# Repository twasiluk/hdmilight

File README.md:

hdmilight
=========

[2016-03-23] This repo has been obsolete for a long time.

Go to http://hacks.esar.org.uk/hdmi-light-v2/ and https://github.com/esar
*************************

Papilio FPGA HDMI Ambilight project forked from http://hacks.esar.org.uk/hg/hdmilight/file/tip/

For latest version, go to http://hacks.esar.org.uk/hdmi-light/

How to use:

1) Manufacture the HDMI receiver board that can be found in the 'board' directory (CADSoft Eagle format)

2) Open the 'fpga/hdmilight.xise' project in Xilinx ISE

2a) Regenerate the IP cores: in the Hierarchy panel, expand the tree and select the conf, line_buffer and resultBuffer entries one by one and run the "Regenerate Core" process in the panel below

2b) Generate the bit file

3) Edit 'firmware/config_lights.h' to set light definitions

4) Edit 'Makefile' in the top level directory and set the DATA2MEM path for the Xilinx data2mem tooli location on your system

5) Run 'make' in the top level directory, which will build 'tools/makemem', then the firmware image, then merge the firware image into the fpga bitfile. The final result should be hdmilight.bit in the top level directory

6) Upload hdmilight.bit to a Papilio One 250K FPGA board

7) Install the HDMI receiver board on to the Papilio board

8) Connect LED strips to output pins

9) Open a serial terminal to the Papilio

10) Give the command to initialise I2C: I I
   
11) Give the command to configure the light definitions and the ADV611 chip: I C

12) Connect HDMI source to receiver board

13) It should now be working

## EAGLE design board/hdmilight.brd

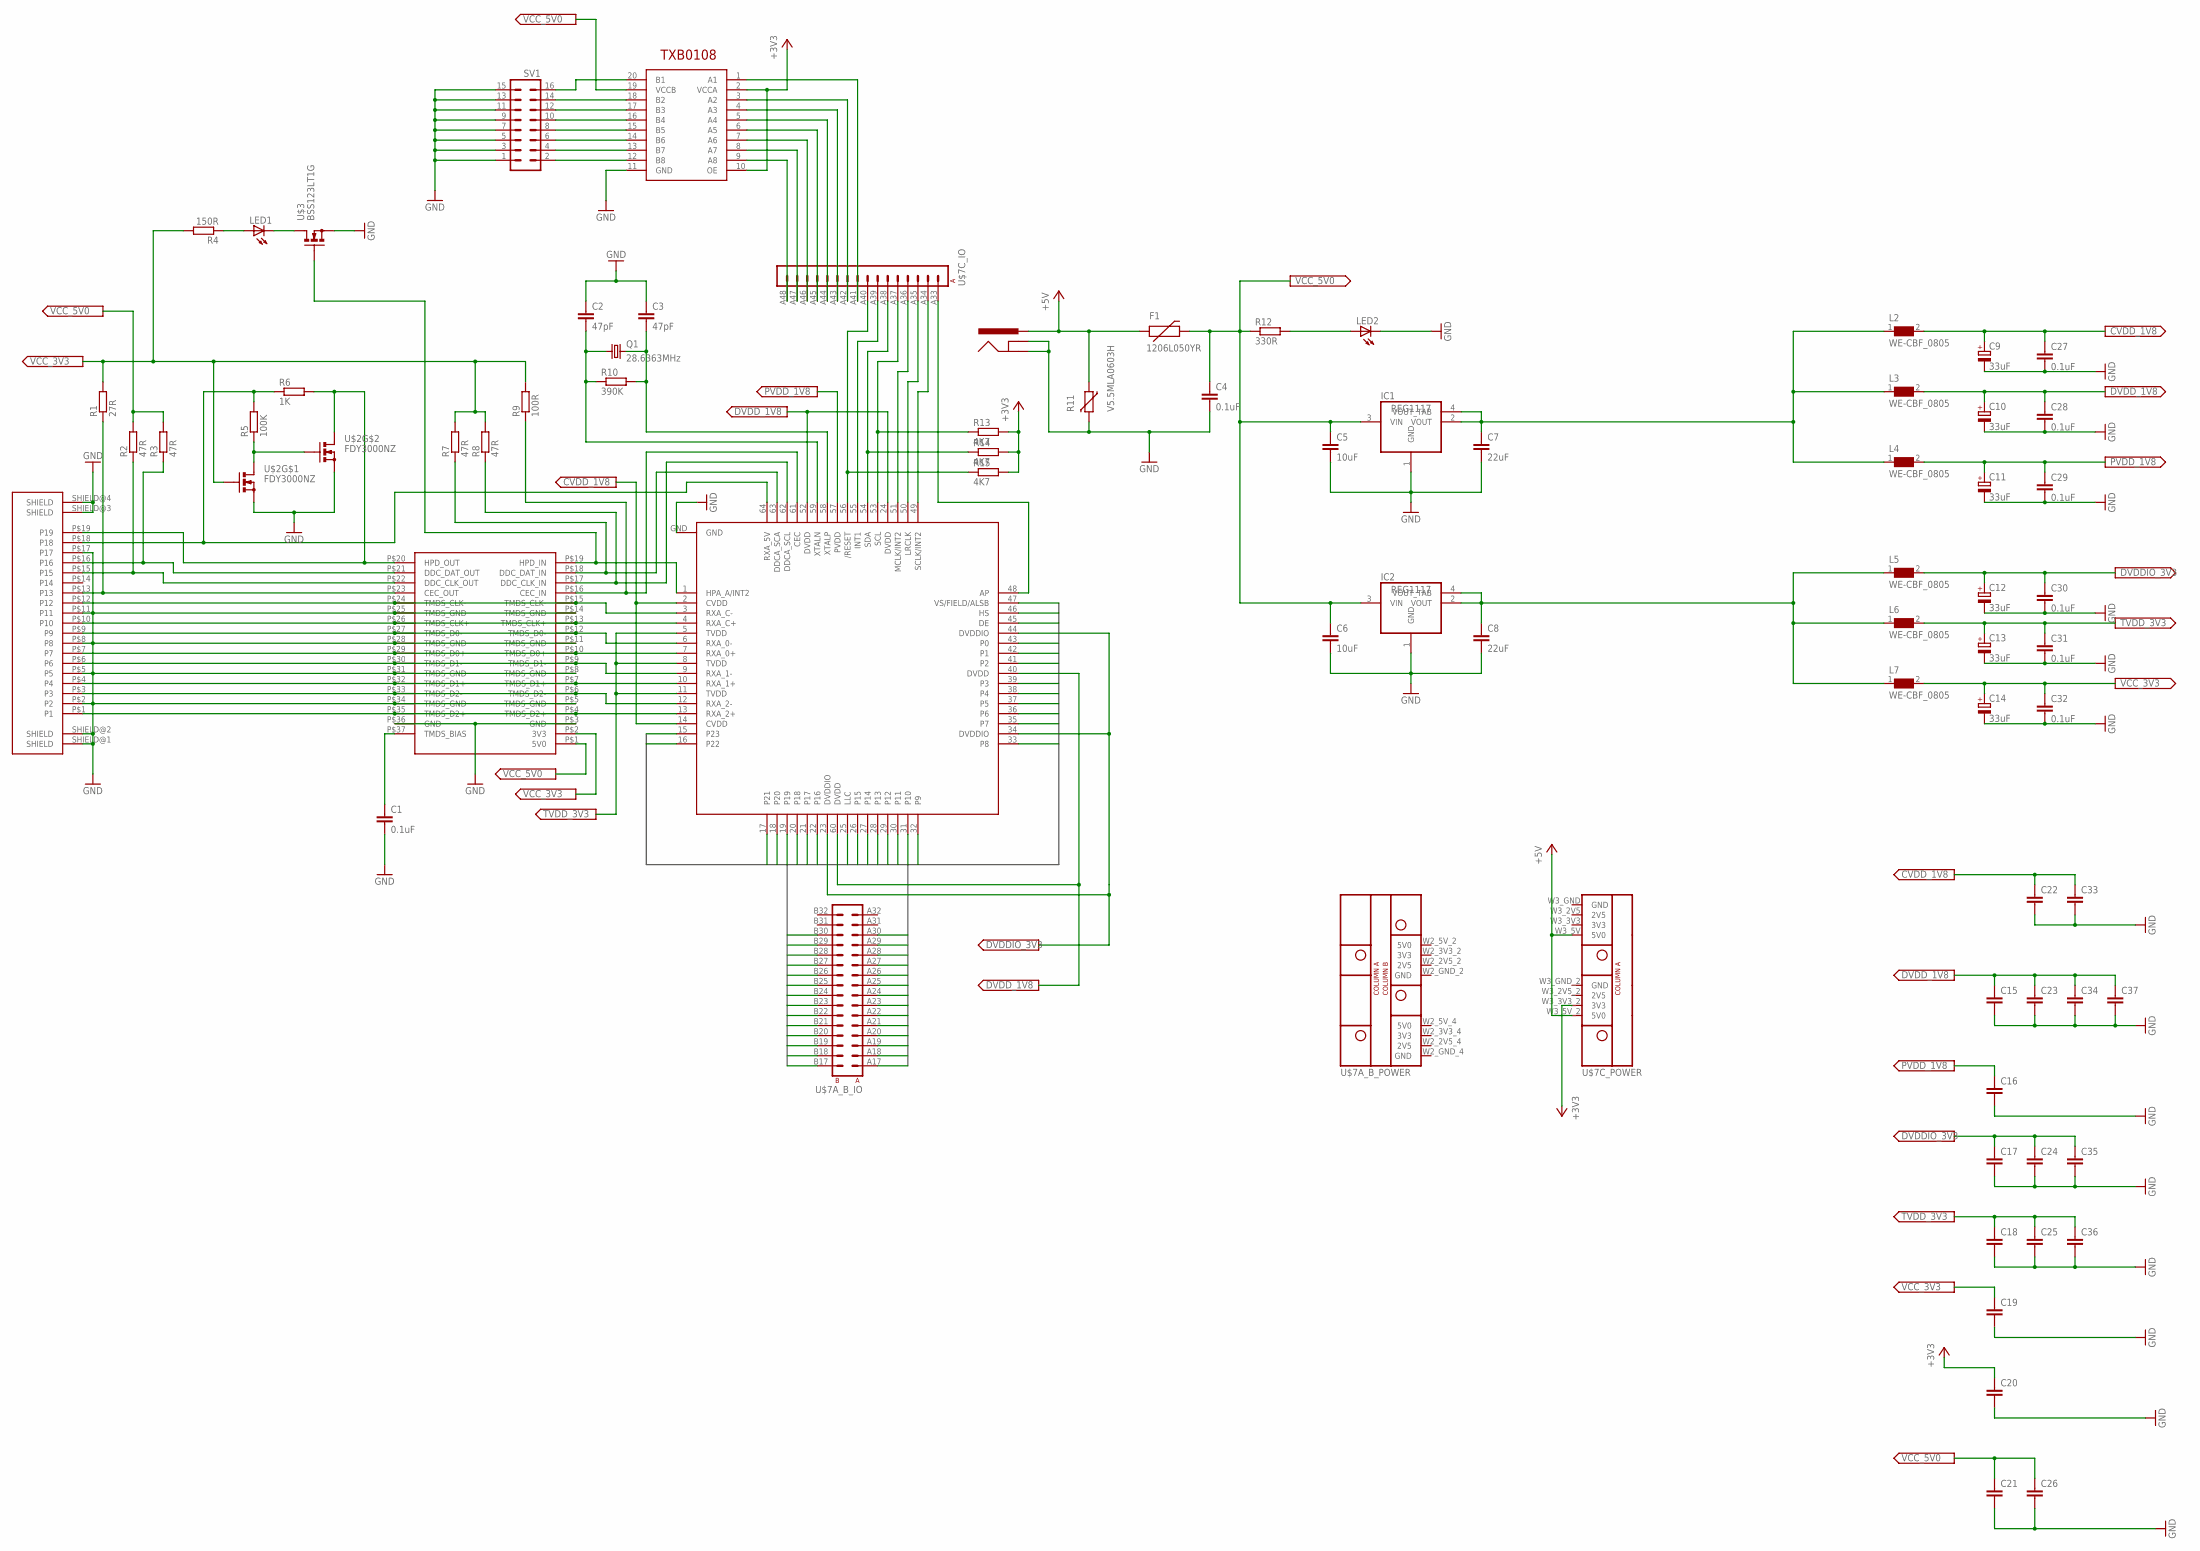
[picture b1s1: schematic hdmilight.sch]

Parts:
C1, C4, C27, C28, C29, C30, C31, C32: 0.1uF; C0603; MPN 02016D104KAT2A
C2, C3: 47pF; C0603; MPN 02013A470JAT2A
C5, C6: 10uF; C1210; MPN 06034D106MAT2A
C7, C8: 22uF; C1206; MPN 06034D226MAT2A
C9, C10, C11, C12, C13, C14: 33uF; SMC_B; MPN 100ZLJ33M8X11.5
C15, C18, C23, C25, C34, C36, C37: C-EUC0402; C0402; MPN 04025A150JAT2A
C16, C17, C19, C20, C21, C22, C24, C26, C33, C35: C-EUC0603; C0603; MPN 06031A100JAT2A
F1: 1206L050YR; PTC-1206; MPN 1206L050YR
IC1, IC2: REG1117; SOT223
J1: POWER_JACKPTH; POWER_JACK_PTH
L2, L3, L4, L5, L6, L7: WE-CBF_0805; 0805
LED1, LED2: LEDCHIP-LED0805; CHIP-LED0805
Q1: 28.6363MHz; SM49
R1: 27R; R0603
R2, R3, R7, R8: 47R; R0603
R4: 150R; R0603
R5: 100K; R0603; MPN 04025A100KAT2A
R6: 1K; R0603; MPN 11AA010-I/P
R9: 100R; R0603; MPN 010010TD
R10: 390K; R0603
R11: V5.5MLA0603H; CT/CN0603
R12: 330R; R0603
R13, R14, R15: 4K7; R0603
SV1: MA08-2
U$1: FCI_HDMI_SOCKET_10029449-001RCF
U$2: FDY3000NZ; SC89-6
U$3: BSS123LT1G; SOT23
U$4: IP4776CZ38; TSSOP38
U$5: TXB0108; TSSOP20
U$6: ADV7611; TQFP64-10X10
U$7: MEGAWING_FULL_P1MEGAWING_P1; MEGAWING_FULL_NOHOLES_P1

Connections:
+3V3: C20.1, R13.2, R14.2, R15.2, U$5.2 (VCCA), U$5.10 (OE), U$7.W3_3V3_2 (3V3)
+5V: F1.1, J1.PWR, R11.1, U$7.W3_5V (5V0), U$7.W3_5V_2 (5V0)
CVDD_1V8: C9.+, C22.1, C27.1, C33.1, L2.2, U$6.2 (CVDD), U$6.14 (CVDD)
DE: U$6.45 (DE), U$7.B18 (B2)
DVDDIO_3V3: C12.+, C17.1, C24.1, C30.1, C35.1, L5.2, U$6.23 (DVDDIO), U$6.34 (DVDDIO), U$6.44 (DVDDIO)
DVDD_1V8: C10.+, C15.1, C23.1, C28.1, C34.1, C37.1, L3.2, U$6.24 (DVDD), U$6.40 (DVDD), U$6.52 (DVDD), U$6.60 (DVDD)
GND: C1.2, C2.1, C3.1, C4.2, C5.2, C6.2, C7.2, C8.2, C9.-, C10.-, C11.-, C12.-, C13.-, C14.-, C15.2, C16.2, C17.2, C18.2, C19.2, C20.2, C21.2, C22.2, C23.2, C24.2, C25.2, C26.2, C27.2, C28.2, C29.2, C30.2, C31.2, C32.2, C33.2, C34.2, C35.2, C36.2, C37.2, IC1.1 (GND), IC2.1 (GND), J1.GND, J1.GNDBREAK, LED2.C, R11.2, SV1.1, SV1.3, SV1.5, SV1.7, SV1.9, SV1.11, SV1.13, SV1.15, U$1.P$2 (P2), U$1.P$5 (P5), U$1.P$8 (P8), U$1.P$11 (P11), U$1.P$17 (P17), U$1.SHIELD@1 (SHIELD), U$1.SHIELD@2 (SHIELD), U$1.SHIELD@3 (SHIELD), U$1.SHIELD@4 (SHIELD), U$2.P$1 (S), U$2.P$4 (S), U$3.2 (S), U$4.P$3 (GND), U$4.P$5 (TMDS_GND), U$4.P$8 (TMDS_GND), U$4.P$11 (TMDS_GND), U$4.P$14 (TMDS_GND), U$4.P$25 (TMDS_GND), U$4.P$28 (TMDS_GND), U$4.P$31 (TMDS_GND), U$4.P$34 (TMDS_GND), U$4.P$36 (GND), U$5.11 (GND), U$6.GND, U$7.W2_GND_2 (GND), U$7.W2_GND_4 (GND), U$7.W3_GND (GND), U$7.W3_GND_2 (GND)
HS: U$6.46 (HS), U$7.A17 (A1)
LLC: U$6.25 (LLC), U$7.A26 (A10)
unnamed: U$1.P$1 (P1), U$4.P$4 (TMDS_D2+), U$4.P$35 (TMDS_D2+), U$6.13 (RXA_2+)
unnamed: U$1.P$3 (P3), U$4.P$6 (TMDS_D2-), U$4.P$33 (TMDS_D2-), U$6.12 (RXA_2-)
unnamed: U$1.P$4 (P4), U$4.P$7 (TMDS_D1+), U$4.P$32 (TMDS_D1+), U$6.10 (RXA_1+)
unnamed: U$1.P$6 (P6), U$4.P$9 (TMDS_D1-), U$4.P$30 (TMDS_D1-), U$6.9 (RXA_1-)
unnamed: U$1.P$7 (P7), U$4.P$10 (TMDS_D0+), U$4.P$29 (TMDS_D0+), U$6.7 (RXA_0+)
unnamed: U$1.P$9 (P9), U$4.P$12 (TMDS_D0-), U$4.P$27 (TMDS_D0-), U$6.6 (RXA_0-)
unnamed: U$1.P$10 (P10), U$4.P$13 (TMDS_CLK+), U$4.P$26 (TMDS_CLK+), U$6.4 (RXA_C+)
unnamed: U$1.P$12 (P12), U$4.P$15 (TMDS_CLK-), U$4.P$24 (TMDS_CLK-), U$6.3 (RXA_C-)
unnamed: R1.1, U$1.P$13 (P13), U$4.P$23 (CEC_OUT)
unnamed: R2.1, U$1.P$15 (P15), U$4.P$22 (DDC_CLK_OUT)
unnamed: R3.1, U$1.P$16 (P16), U$4.P$21 (DDC_DAT_OUT)
unnamed: R6.2, U$1.P$19 (P19), U$2.P$3 (D), U$4.P$20 (HPD_OUT)
unnamed: SV1.2, U$5.12 (B8)
unnamed: LED2.A, R12.2
unnamed: R8.1, U$4.P$17 (DDC_CLK_IN), U$6.62 (DDCA_SCL)
unnamed: C8.1, IC2.2 (VOUT), IC2.4 (VOUT_TAB), L5.1, L6.1, L7.1
unnamed: C7.1, IC1.2 (VOUT), IC1.4 (VOUT_TAB), L2.1, L3.1, L4.1
unnamed: R7.1, U$4.P$18 (DDC_DAT_IN), U$6.63 (DDCA_SCA)
unnamed: R9.1, U$4.P$16 (CEC_IN), U$6.61 (CEC)
unnamed: C2.2, Q1.1, R10.1, U$6.59 (XTALN)
unnamed: C3.2, Q1.2, R10.2, U$6.58 (XTALP)
unnamed: U$6.49 (SCLK/INT2), U$7.A34 (A2)
unnamed: U$6.50 (LRCLK), U$7.A35 (A3)
unnamed: U$6.48 (AP), U$7.A33 (A1)
unnamed: R13.1, U$6.53 (SCL), U$7.A37 (A5)
unnamed: R14.1, U$6.54 (SDA), U$7.A38 (A6)
unnamed: U$6.55 (INT1), U$7.A39 (A7)
unnamed: R15.1, U$6.56 (/RESET), U$7.A40 (A8)
unnamed: C1.1, U$4.P$37 (TMDS_BIAS)
unnamed: U$5.9 (A8), U$7.A48 (A16)
unnamed: U$5.8 (A7), U$7.A47 (A15)
unnamed: U$5.7 (A6), U$7.A46 (A14)
unnamed: U$5.6 (A5), U$7.A45 (A13)
unnamed: U$5.5 (A4), U$7.A44 (A12)
unnamed: U$5.4 (A3), U$7.A43 (A11)
unnamed: U$5.3 (A2), U$7.A42 (A10)
unnamed: U$6.51 (MCLK/INT2), U$7.A36 (A4)
unnamed: SV1.14, U$5.18 (B2)
unnamed: SV1.12, U$5.17 (B3)
unnamed: SV1.10, U$5.16 (B4)
unnamed: SV1.8, U$5.15 (B5)
unnamed: SV1.6, U$5.14 (B6)
unnamed: SV1.4, U$5.13 (B7)
unnamed: U$5.1 (A1), U$7.A41 (A9)
unnamed: SV1.16, U$5.20 (B1)
unnamed: R5.1, U$2.P$5 (G), U$2.P$6 (D)
unnamed: R5.2, R6.1, U$1.P$18 (P18), U$6.64 (RXA_5V)
unnamed: LED1.A, R4.1
unnamed: LED1.C, U$3.3 (D)
unnamed: U$3.1 (G), U$4.P$19 (HPD_IN), U$6.1 (HPA_A/INT2)
P0: U$6.43 (P0), U$7.A18 (A2)
P1: U$6.42 (P1), U$7.B19 (B3)
P2: U$6.41 (P2), U$7.A19 (A3)
P3: U$6.39 (P3), U$7.B20 (B4)
P4: U$6.38 (P4), U$7.A20 (A4)
P5: U$6.37 (P5), U$7.B21 (B5)
P6: U$6.36 (P6), U$7.A21 (A5)
P7: U$6.35 (P7), U$7.B22 (B6)
P8: U$6.33 (P8), U$7.A22 (A6)
P9: U$6.32 (P9), U$7.B23 (B7)
P10: U$6.31 (P10), U$7.A23 (A7)
P11: U$6.30 (P11), U$7.B24 (B8)
P12: U$6.29 (P12), U$7.A24 (A8)
P13: U$6.28 (P13), U$7.B25 (B9)
P14: U$6.27 (P14), U$7.A25 (A9)
P15: U$6.26 (P15), U$7.B26 (B10)
P16: U$6.22 (P16), U$7.B27 (B11)
P17: U$6.21 (P17), U$7.A27 (A11)
P18: U$6.20 (P18), U$7.B28 (B12)
P19: U$6.19, U$7.A28 (A12)
P20: U$6.18 (P20), U$7.B29 (B13)
P21: U$6.17 (P21), U$7.A29 (A13)
P22: U$6.16 (P22), U$7.B30 (B14)
P23: U$6.15 (P23), U$7.A30 (A14)
PVDD_1V8: C11.+, C16.1, C29.1, L4.2, U$6.57 (PVDD)
TVDD_3V3: C13.+, C18.1, C25.1, C31.1, C36.1, L6.2, U$6.5 (TVDD), U$6.8 (TVDD), U$6.11 (TVDD)
VCC_3V3: C14.+, C19.1, C32.1, L7.2, R1.2, R4.2, R7.2, R8.2, R9.2, U$2.P$2 (G), U$4.P$2 (3V3)
VCC_5V0: C4.1, C5.1, C6.1, C21.1, C26.1, F1.2, IC1.3 (VIN), IC2.3 (VIN), R2.2, R3.2, R12.1, U$4.P$1 (5V0), U$5.19 (VCCB)
VS: U$6.47 (VS/FIELD/ALSB), U$7.B17 (B1)

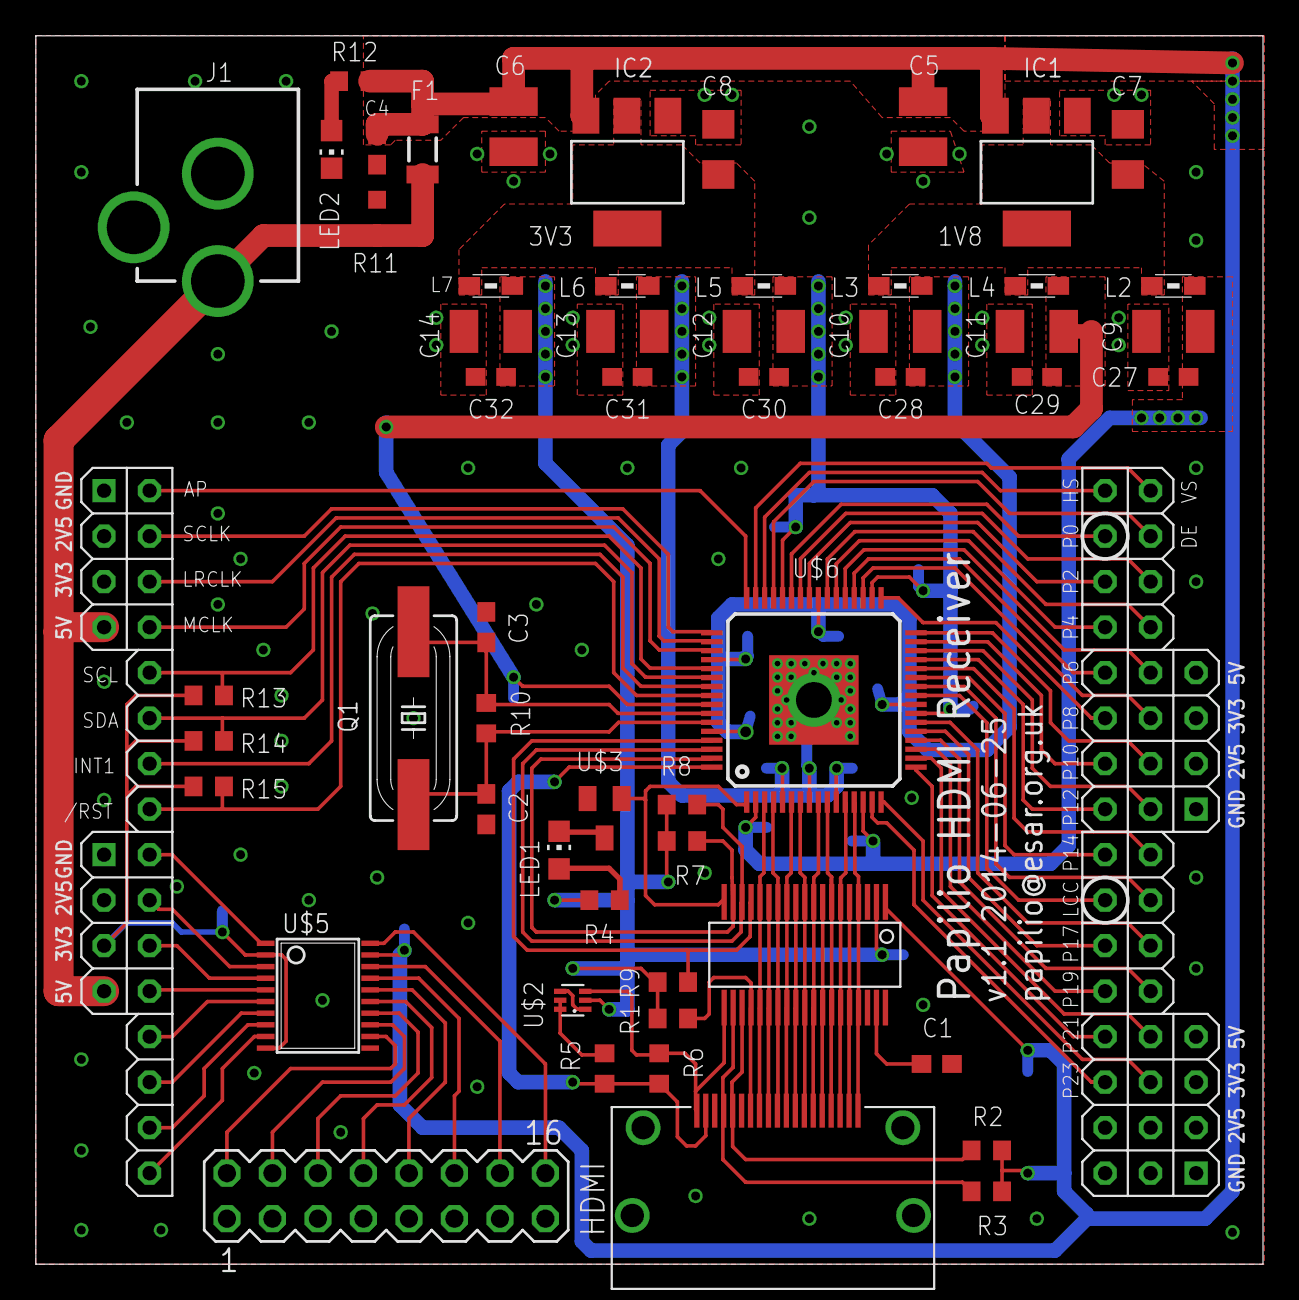
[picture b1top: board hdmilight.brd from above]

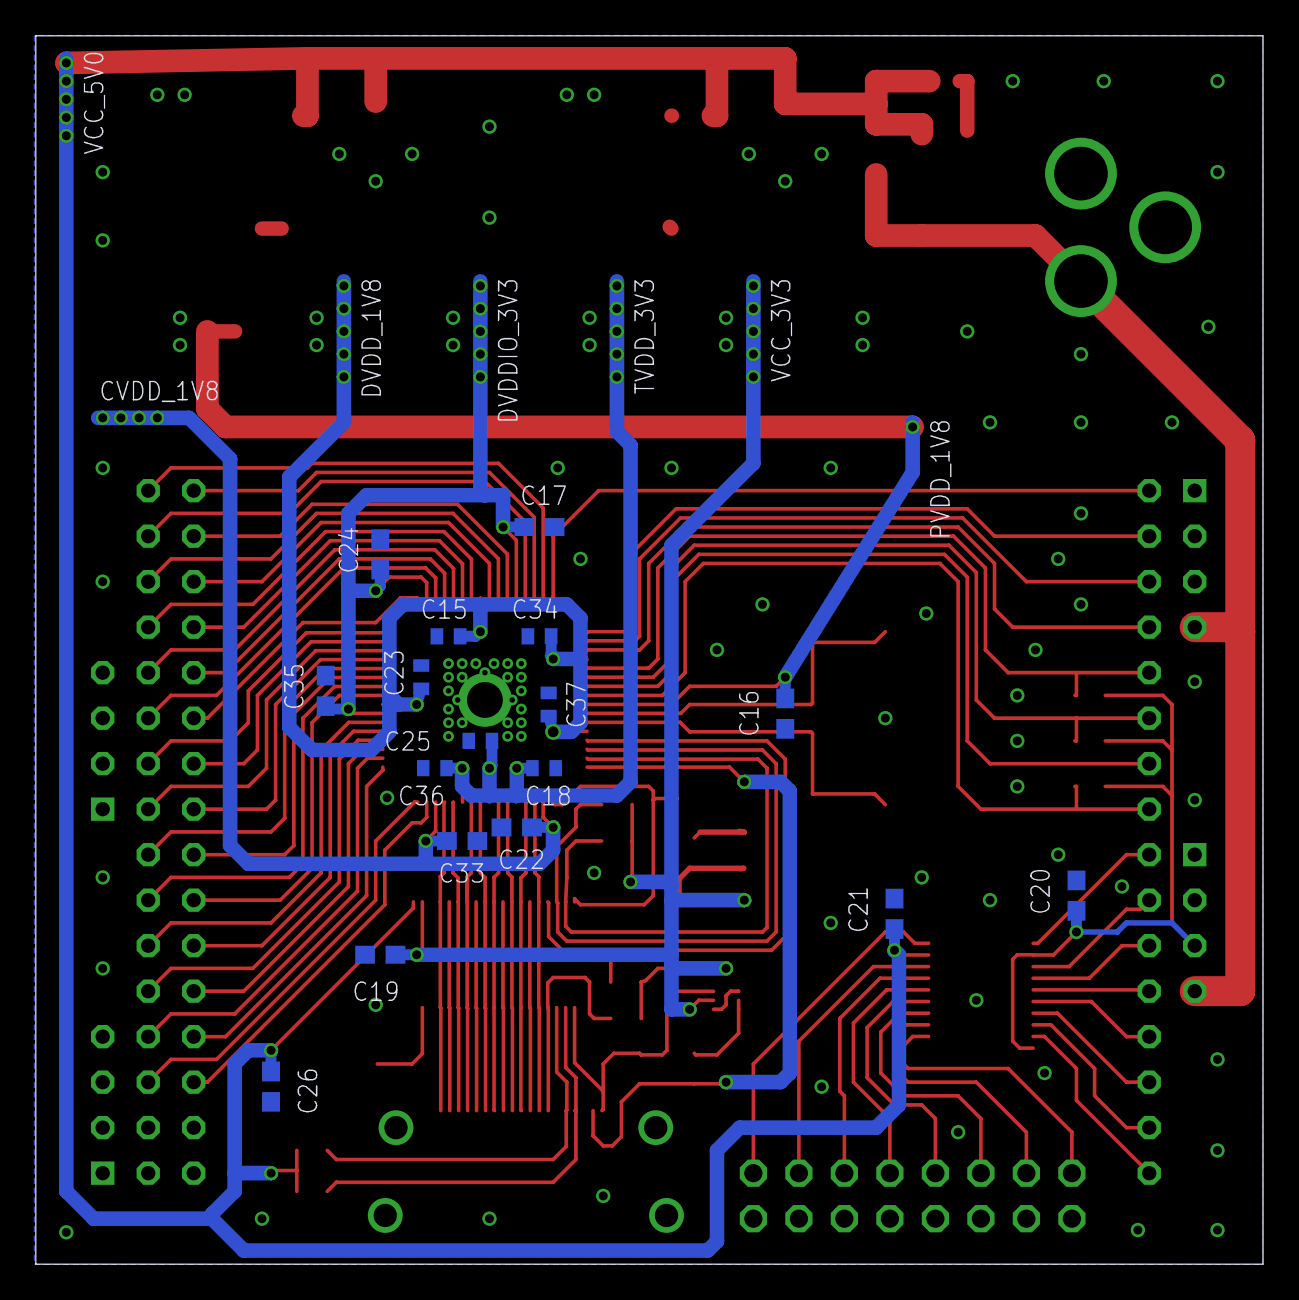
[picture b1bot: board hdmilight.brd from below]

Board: 2 copper layers, 68.5 x 68.6 mm, 73 parts (17 on the bottom side), 88 nets.

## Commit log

2014-06-24 Update README.md
    Reference links
2014-06-24 datasheets
2014-06-24 lowercase directory name
2014-06-25 import from http://hacks.esar.org.uk/hg/hdmilight/file/tip/
2014-06-25 move README to README.md
2014-06-25 assembled board pictures
2014-06-25 fixed DC plug VCC/GND connection
2014-06-25 Update README.md
    formatting
2014-06-25 updated gerbers and schematic after DC jack VCC/GND fix
2014-06-25 dc jack
2014-06-25 board version changed to 1.1
2014-06-26 FDY3000NZ datasheet
2014-07-04 V5.5MLA varistor datasheet
2014-07-04 1117 voltage regulator
2014-08-17 adding a "regenerate cores" step to the readme
2014-08-17 UCF for Papilio Pro (Spartan 6)
2014-09-17 Fixed firmware build errors with avr-gcc 4.8 [from esar.org.uk]
2016-03-23 redirect to version 2

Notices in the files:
parts and their libraries:
EagleLibrary_Wuerth_Elektronik_eiSos_Ver: Copyright: Würth Elektronik
